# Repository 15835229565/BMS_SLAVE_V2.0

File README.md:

BMS_SLAVE_V2.0
==============

ATtiny13 sourec code for HW version 2.0

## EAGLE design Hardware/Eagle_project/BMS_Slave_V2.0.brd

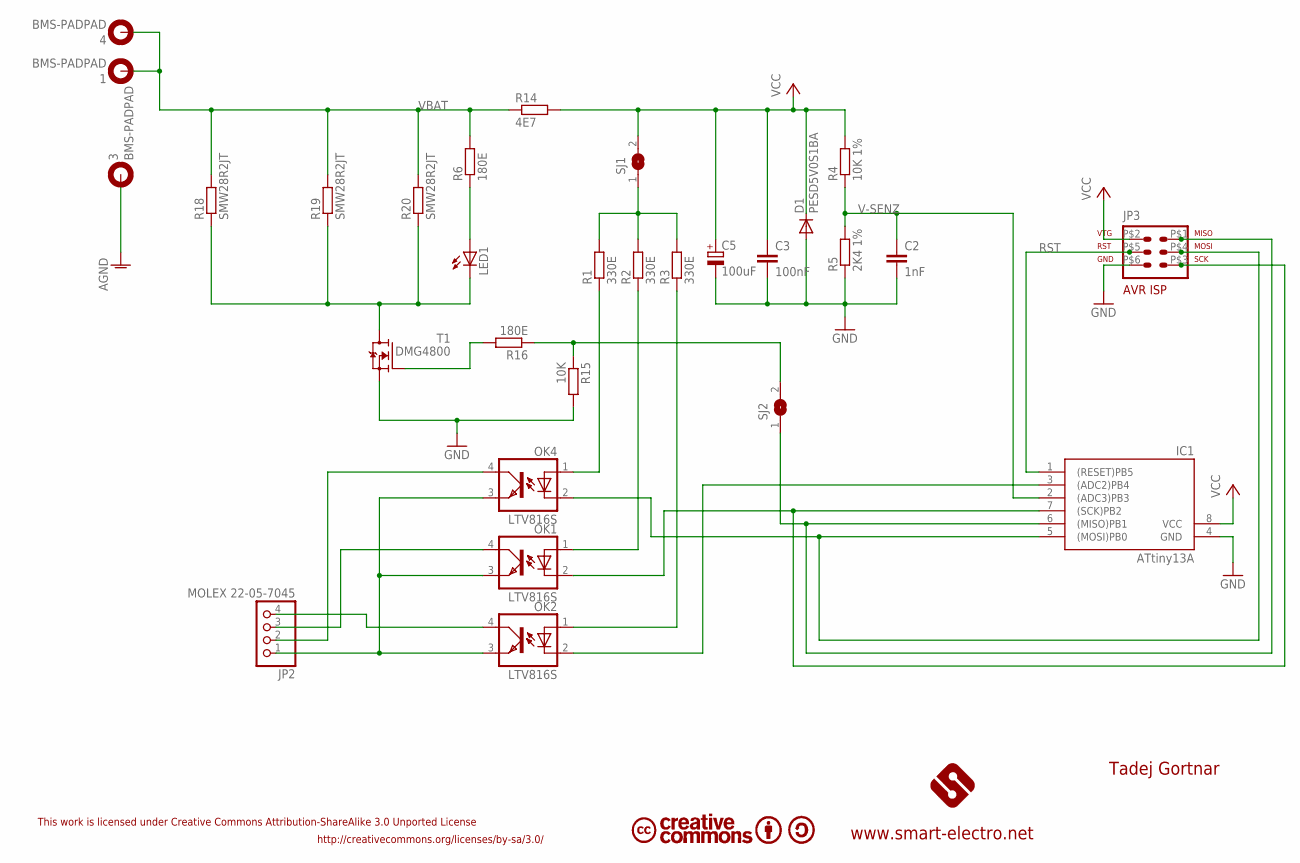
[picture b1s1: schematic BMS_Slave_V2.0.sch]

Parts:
1, 3, 4: BMS-PADPAD; BMSPAD
C2: 1nF; C0805K
C3: 100nF; C0805K
C5: 100uF; 153CLV-0605
D1: PESD5V0S1BA; SOD323-W
IC1: ATtiny13A; SO08
JP2: MOLEX 22-05-7045; 1X04
JP3: AVR-ISP-6S; 6PAD_ISP_SMD
LED1: LEDCHIP-LED0805; CHIP-LED0805
OK1, OK2, OK4: LTV816S; SMD4
R1, R2, R3: 330E; M0805
R4: 10K 1%; M0805
R5: 2K4 1%; M0805
R6, R16: 180E; M0805
R14: 4E7; M0805
R15: 10K; M0805
R18, R19, R20: SMW28R2JT; R2512W
SJ1, SJ2: SJ
T1: DMG4800; TO252

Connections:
AGND: 3.B5,5
GND: C2.2, C3.2, C5.-, D1.A, IC1.4 (GND), JP3.P$6 (6), R5.1, R15.2, T1.2 (S)
MISO: IC1.6 ((MISO)PB1), JP3.P$1 (1), SJ2.1
MOSI: IC1.5 ((MOSI)PB0), JP3.P$4 (4), OK4.2 (C)
unnamed: JP2.2, OK4.4 (COL)
unnamed: JP2.3, OK1.4 (COL)
unnamed: JP2.4, OK2.4 (COL)
unnamed: R1.2, R2.2, R3.2, SJ1.1
unnamed: LED1.C, R18.1, R19.1, R20.1, T1.3 (D)
unnamed: JP2.1, OK1.3 (EMIT), OK2.3 (EMIT), OK4.3 (EMIT)
unnamed: R16.2, T1.1 (G)
unnamed: R15.1, R16.1, SJ2.2
unnamed: OK4.1 (A), R1.1
unnamed: OK1.1 (A), R2.1
unnamed: OK2.1 (A), R3.1
unnamed: LED1.A, R6.1
unnamed: IC1.3 ((ADC2)PB4), OK2.2 (C)
RST: IC1.1 ((RESET)PB5), JP3.P$5 (5)
SCK: IC1.7 ((SCK)PB2), JP3.P$3 (3), OK1.2 (C)
V-SENZ: C2.1, IC1.2 ((ADC3)PB3), R4.1, R5.2
VBAT: 1.B5,5, 4.B5,5, R6.2, R14.1, R18.2, R19.2, R20.2
VCC: C3.1, C5.+, D1.C, IC1.8 (VCC), JP3.P$2 (2), R4.2, R14.2, SJ1.2

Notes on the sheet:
www.smart-electro.net
http://creativecommons.org/licenses/by-sa/3.0/
Tadej Gortnar
This work is licensed under Creative Commons Attribution-ShareAlike 3.0 Unported License

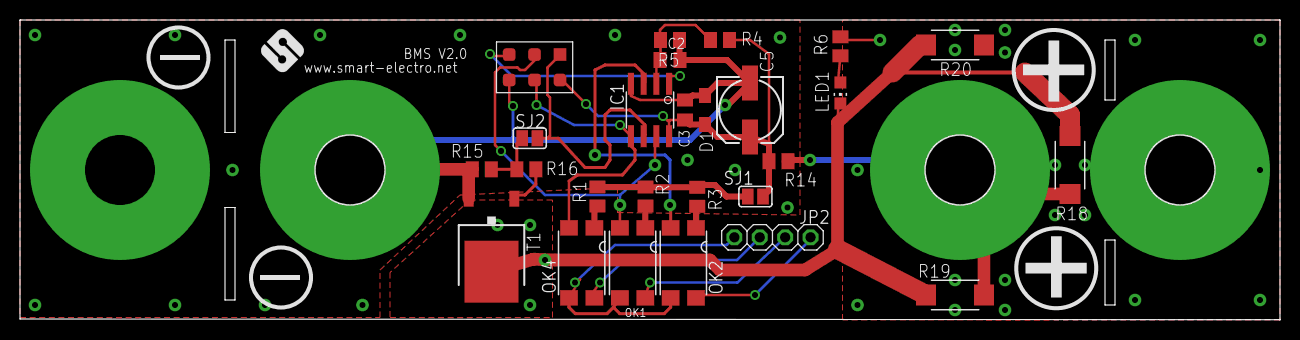
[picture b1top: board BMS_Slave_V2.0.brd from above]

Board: 2 copper layers, 126.0 x 30.0 mm, 29 parts (0 on the bottom side), 21 nets.

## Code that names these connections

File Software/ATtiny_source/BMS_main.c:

#include <avr/interrupt.h>
#include <avr/pgmspace.h>
#include <avr/wdt.h>
#include <avr/eeprom.h>


#define SET |=
#define CLR &=~
#define TOG ^=

#define CMPINT_EN_MASK    ((1<<OCIE0A) | (0<<OCIE0B)) // INT on Comp-A

//#define SOFTUART_PRESCALE (8)
#define SOFTUART_PRESCALE (1)

#if (SOFTUART_PRESCALE==8)
#define PRESC_MASKA         (0)
#define PRESC_MASKB         (1<<CS01)
#elif (SOFTUART_PRESCALE==1)
#define PRESC_MASKA         (0)
#define PRESC_MASKB         (1<<CS00)
#else 
#error "prescale unsupported"
#endif

// 1 Startbit, 8 Databits, 1 Stopbit = 10 Bits/Frame
// A timer interrupt must be set to interrupt at three times the required baud rate.
#define SOFTUART_BAUD_RATE 1200
#define F_CPU 1200000

//#define TIMERTOP (F_CPU/SOFTUART_PRESCALE/SOFTUART_BAUD_RATE/3 -1)
#define TIMERTOP (F_CPU/SOFTUART_PRESCALE/SOFTUART_BAUD_RATE/6 -1) // Corect PWM
#define TX_NUM_OF_BITS (10)
#define SU_TRUE 1
#define SU_FALSE 0

#define SOFTUART_TXPORT  PORTB
#define SOFTUART_TXDDR   DDRB
#define SOFTUART_TXBIT   PB0

volatile static unsigned char  flag_tx_ready;
volatile static unsigned char  timer_tx_ctr;
volatile static unsigned char  bits_left_in_tx;
volatile static unsigned short internal_tx_buffer; /* ! mt: was type uchar - this was wrong */

#define set_tx_pin_high() (SOFTUART_TXPORT SET (1<<SOFTUART_TXBIT))
#define set_tx_pin_low()  (SOFTUART_TXPORT CLR (1<<SOFTUART_TXBIT))

// ADC Definicije
#define Li_Full (704) // 4,20V 
#define Li_Over (670) // 4,00V
#define Li_Good (612) // 3,65V
#define Li_Norm (553) // 3,30V 
#define Li_Low  (477) // 2,85V
#define Li_Kill (419) // 2,50V

#define BATTERY_OVER   PB2
#define BATTERY_UNDER  PB4

#define set_over_pin()  (PORTB SET (1<<BATTERY_OVER))
#define clr_over_pin()  (PORTB CLR (1<<BATTERY_OVER))
#define set_under_pin() (PORTB SET (1<<BATTERY_UNDER))
#define clr_under_pin() (PORTB CLR (1<<BATTERY_UNDER))

volatile static unsigned short ADC_result;


#define EE_COMM 0

// MAIN data
volatile unsigned short cnt = 0;
volatile char ADC_done = 0;
volatile char ADC_go = 0;
unsigned char comm_mode = 0;

// INT
ISR(TIM0_COMPA_vect)
{
  char tmp;
// Transmitter Section
  if (flag_tx_ready) 
  {
    tmp = timer_tx_ctr;
    if (--tmp <= 0)
    {
      if (internal_tx_buffer & 0x01) 
      {
        //set_tx_pin_high();
		set_tx_pin_low();
      }
      else 
      {
        //set_tx_pin_low();
		set_tx_pin_high();
      }
      internal_tx_buffer >>= 1;
      tmp = 3;
      if (--bits_left_in_tx <= 0) 
      {
        flag_tx_ready = SU_FALSE;
      }
    }
    timer_tx_ctr = tmp;
  }

// ADC
  if (ADC_go == 1)
  {
    ADCSRA SET (1<<ADSC);   // Start ADC
	ADC_go = 0;
  }

// Timer 
  cnt++;
}

ISR(TIM0_COMPB_vect)
{
//  cnt--;
}

ISR(ADC_vect)
{
  ADC_done = 1;
//  ADCSRA SET (1<<ADSC); Start ADC
}


// SOFT-UART TX
unsigned char softuart_can_transmit( void ) 
{
  return ( flag_tx_ready );
}

void softuart_putchar( const char ch )
{
  while ( flag_tx_ready ) {
		; // wait for transmitter ready
		  // add watchdog-reset here if needed;
  }

	// invoke_UART_transmit
  timer_tx_ctr       = 3;
  bits_left_in_tx    = TX_NUM_OF_BITS;
  internal_tx_buffer = ( ch<<1 ) | 0x200;
  flag_tx_ready      = SU_TRUE;
}
	
void softuart_puts( const char *s )
{
  while ( *s ) {
    softuart_putchar( *s++ );
  }
}
	
void softuart_puts_p( const char *prg_s )
{
  char c;

  while ( ( c = pgm_read_byte( prg_s++ ) ) ) {
    softuart_putchar(c);
  }
}

// INIT
void adc_init()
{
//  Initialise registers. Note that the compiler optimises each to an integer, so the 0s just make life easier.
//  ADMUX = (0<<REFS0) | (0<<ADLAR) | (0<<MUX1) | (0<<MUX0); // VCC=VREF, PB5 input MUX
//  ADMUX = (1<<REFS0) | (0<<ADLAR) | (1<<MUX1) | (1<<MUX0);   // 1.1V=VREF, PB5 input MUX

//  ADCSRA = (1<<ADEN) | (0<<ADSC) | (0<<ADATE) | (0<<ADIF) | (0<<ADIE) | (1<<ADPS2) | (0<<ADPS1) | (0<<ADPS0);

//  DIDR0 = (1<<ADC0D) | (0<<ADC1D) | (0<<ADC2D ) | (0<<ADC3D); // ADC0 input buffer OFF
//  DIDR0 = (0<<ADC0D) | (0<<ADC1D) | (0<<ADC2D ) | (1<<ADC3D);   // ADC0 input buffer OFF





  ADMUX = (1<<REFS0) | (0<<ADLAR) | (1<<MUX1) | (1<<MUX0);   // 1.1V=VREF, PB3 input MUX

  ADCSRA = (1<<ADEN) | (0<<ADSC) | (0<<ADATE) | (0<<ADIF) | (0<<ADIE) | (1<<ADPS2) | (0<<ADPS1) | (0<<ADPS0);

  //  DIDR0 = (1<<ADC0D) | (0<<ADC1D) | (0<<ADC2D ) | (0<<ADC3D); // ADC0 input buffer OFF
  DIDR0 = (0<<ADC0D) | (0<<ADC1D) | (0<<ADC2D ) | (1<<ADC3D);   // ADC0 input buffer OFF

//  Initialise ADC, ignore first result
  ADCSRA SET (1<<ADSC);      // START ACDC
  while( ADCSRA & (1<<ADSC) ) {} // Pool ADC

  //ADCSRB = (0<<ADTS2) | (1<<ADTS1) | (1<<ADTS0 );
  //ADCSRA SET (1<<ADIE);      // Enable ADC interrupt
  //ADCSRA SET (1<<ADATE);     // Enable ADC timer trigger
  
  ADCSRB = (0<<ADTS2) | (1<<ADTS1) | (1<<ADTS0 );
  ADCSRA SET (1<<ADIE);      // Enable ADC interrupt  
  
// ADCSRA SET (1<<ADSC);     // START ACD
}

static void timer_init(void)
{
  unsigned char sreg_tmp;
	
  sreg_tmp = SREG;
  cli();
CLKPR=0b10000011;	
  OCR0A = TIMERTOP;          /* set top */
  OCR0B = 0;                 /* set PWM-B */

  TCCR0A = PRESC_MASKA | (1<<WGM00) | (1<<COM0B1) | (0<<COM0B0);
  TCCR0B = PRESC_MASKB | (1<<WGM02);

  TIMSK0 |= CMPINT_EN_MASK;

  TCNT0 = 0;                 /* reset counter */
	
  SREG = sreg_tmp;
}


// EEPROM
void EEPROM_write(unsigned char ucAddress, unsigned char ucData)
{

  while(EECR & (1<<EEWE));             // Wait for completion of previous write

  EECR = (0<<EEPM1)|(0>>EEPM0);        // Set Programming mode

  EEARL = ucAddress;                   // Set up address and data registers
  
  EEDR = ucData;
  
  EECR |= (1<<EEMWE);                  // Write logical one to EEMPE

  EECR |= (1<<EEWE);                   // Start eeprom write by setting EEPE
}

unsigned char EEPROM_read(unsigned char ucAddress)
{

  while(EECR & (1<<EEWE));             // Wait for completion of previous write

  EEARL = ucAddress;                   // Set up address register

  EECR |= (1<<EERE);                   // Start eeprom read by writing EERE

  return EEDR;                         // Return data from data register
}

// Pomozne funkcije

char to_hex(char bits4)
{
  char tp_bits;
  tp_bits = bits4 & 0x0F;
  if (tp_bits <= 9)
  {
    return(48 + tp_bits);
  }
  else
  {
    return(55 + tp_bits);
  }
}

void send_adc()
{
     // softuart_putchar( '>' );
      //softuart_putchar(to_hex(ADC_result >> 8));
      //softuart_putchar(to_hex(ADC_result >> 4));
      //softuart_putchar(to_hex(ADC_result & 0x000F));
     // softuart_putchar( '\r' );
	 softuart_putchar(0b10101010);
}

// MAIN
int main(void)
{
volatile unsigned char ad_H, ad_L;

  wdt_enable(WDTO_2S);       // Set WDT for 2sek
  wdt_reset();               // Reset WDT.

  //DDRB = 0xFF;
  DDRB = 0x37;
  
  comm_mode = EEPROM_read(EE_COMM);
  set_over_pin();
  set_under_pin();

  flag_tx_ready = SU_FALSE;
  set_tx_pin_high();                   // mt: set to high to avoid garbage on init

  ADC_done = 0;
  ADC_go = 0;

  adc_init();
  timer_init();

  sei();                               // ENABLE interupt

  while (1)
  {
    if (ADC_done == 1)                 // Preveri ali imamo novo meritev napetosti na bateriji
    {
      ADC_done = 0;                    // Zbrisi zastavico za novo meritev
     // ADC_result = (ADCH << 8) + ADCL; // Poberi meritev iz ACD-ja
			ad_L = ADCL;
			ad_H = ADCH;
			softuart_putchar('.');
			softuart_putchar(to_hex(ad_L));
			softuart_putchar(to_hex(ad_H));
			ADC_result = (ad_H << 8) + ad_L; // AD value
			
			

// Baterija polna, konèaj polnjenje
      if (ADC_result > Li_Full) 
      {
        clr_over_pin();
					softuart_putchar('>');

      }else
      {
        set_over_pin();
      }

// Baterija skoraj polna, spuèaj tok mimo
      if (ADC_result > Li_Over) 
      {
     			softuart_putchar('+');

	    if (OCR0B < TIMERTOP) 
        {
          OCR0B++;
        }
      }else
      {
        if (OCR0B > 0) 
        {
          OCR0B--;
        }
      }

// Baterija skoraj prazna, sprozi opozorilo
      if (ADC_result < Li_Low) 
      {
      			softuart_putchar('x');

	  
	    clr_under_pin();;
      }else
      {
        set_under_pin();;
      }
	 
	 // send_adc();                      // Poslji meritev na UART
    }
    if (cnt >= 360)                    // 1/20sek
    {
//        PORTB SET (1<<PB4);
      cnt = 0;
	  ADC_go = 1;                      // Naslednja prekinitev prozi ADC
    } 
    wdt_reset();                       // Kuza pazi "sedi".
	
  }
}

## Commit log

2014-06-29 initail comit
2014-06-29 clean solution
2015-01-06 New software with RC calibarion
2015-01-06 Merge
2015-01-21 Added CRC
2015-01-22 Final version with CRC
